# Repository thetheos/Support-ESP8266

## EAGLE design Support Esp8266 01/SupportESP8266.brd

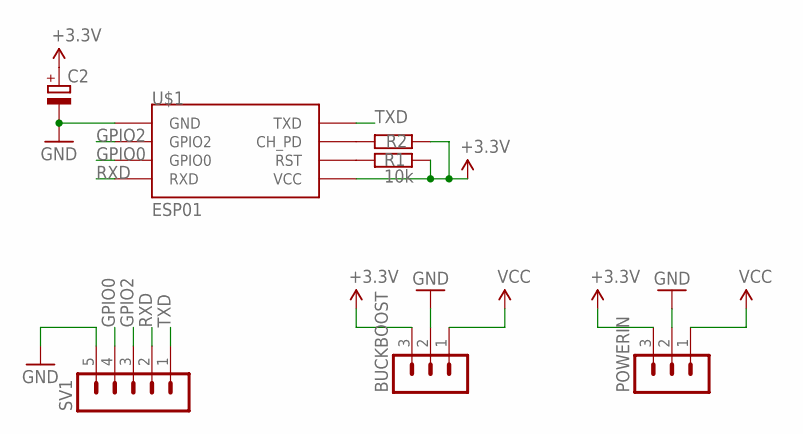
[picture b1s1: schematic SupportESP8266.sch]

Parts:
BUCKBOOST: MA03-1
C2: CPOL-EUE5-10.5; E5-10,5
POWERIN: MA03-1
R1: 10k; 0204/7
R2: R-EU_0204/7; 0204/7
SV1: MA05-1
U$1: ESP01

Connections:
+3.3V: BUCKBOOST.3, C2.+, POWERIN.3, R1.2, R2.2, U$1.VCC
+3V: BUCKBOOST.1, POWERIN.1
GND: BUCKBOOST.2, C2.-, POWERIN.2, SV1.5, U$1.GND
GPIO0: SV1.4, U$1.GPIO0
GPIO2: SV1.3, U$1.GPIO2
unnamed: R1.1, U$1.RST
unnamed: R2.1, U$1.CH_PD
RXD: SV1.2, U$1.RX (RXD)
TXD: SV1.1, U$1.TX (TXD)

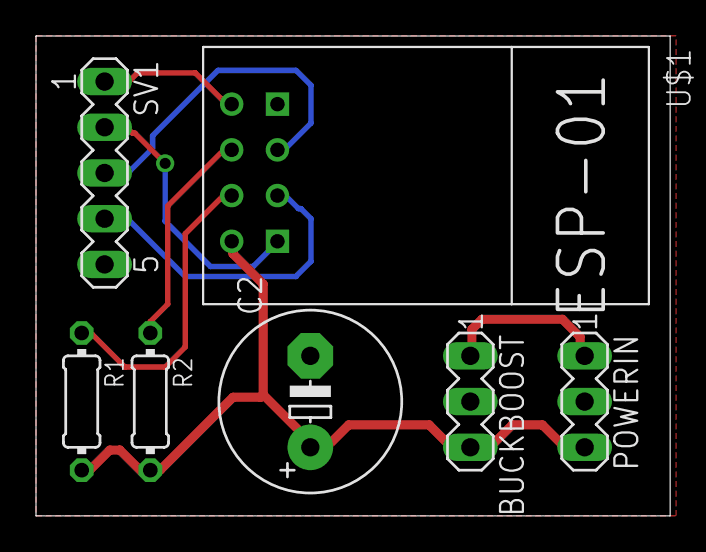
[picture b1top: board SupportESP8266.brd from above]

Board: 2 copper layers, 35.2 x 26.7 mm, 7 parts (0 on the bottom side), 9 nets.

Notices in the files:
parts and their libraries:
SparkFun-Aesthetics: Licensing: Creative Commons ShareAlike 4.0 International - https://creativecommons.org/licenses/by-sa/4.0
